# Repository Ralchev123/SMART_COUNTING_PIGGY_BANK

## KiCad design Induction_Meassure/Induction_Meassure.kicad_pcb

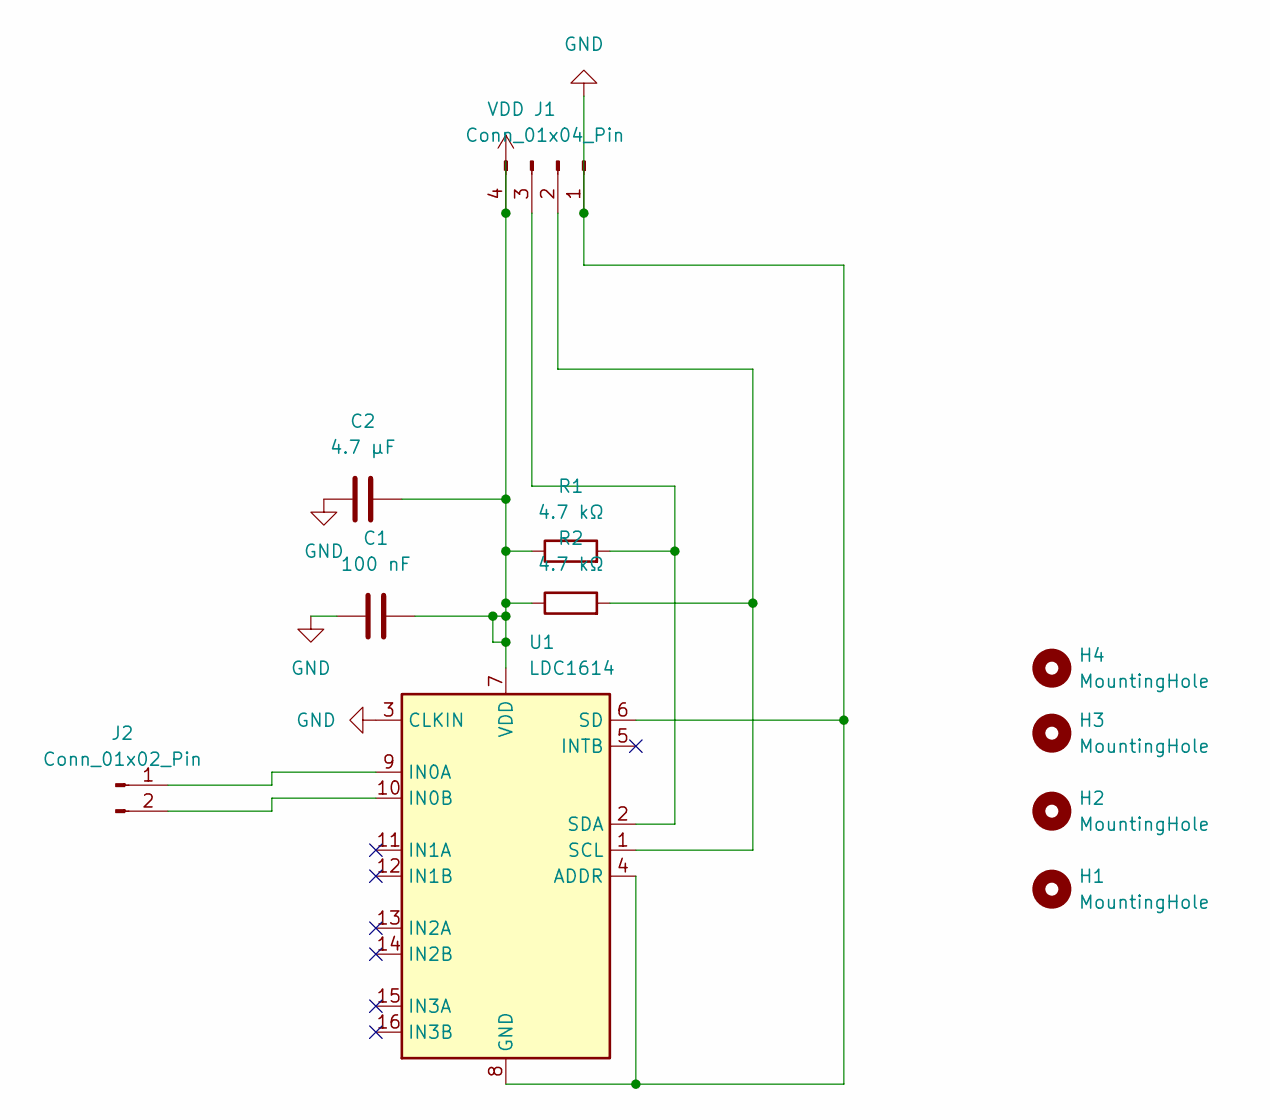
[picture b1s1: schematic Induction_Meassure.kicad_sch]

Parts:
C1: 100 nF; C_0603_1608Metric
C2: 4.7 µF; C_1206_3216Metric
H1, H2, H3, H4: MountingHole; MountingHole_3.2mm_M3
J1: Conn_01x04_Pin; PinHeader_1x04_P2.54mm_Vertical
J2: Conn_01x02_Pin; PinHeader_1x02_P2.54mm_Vertical
R1, R2: 4.7 kΩ; R_0805_2012Metric
U1: LDC1614; WQFN-16-1EP_4x4mm_P0.5mm_EP2.6x2.6mm_ThermalVias

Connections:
GND: C1.1, C2.2, J1.1, U1.3 (CLKIN), U1.4 (ADDR), U1.6 (SD), U1.8 (GND), U1.17 (GND)
unnamed: J1.2, R2.2, U1.1 (SCL)
unnamed: J1.3, R1.2, U1.2 (SDA)
unnamed: J2.1, U1.9 (IN0A)
unnamed: J2.2, U1.10 (IN0B)
VDD: C1.2, C2.1, J1.4, R1.1, R2.1, U1.7 (VDD)

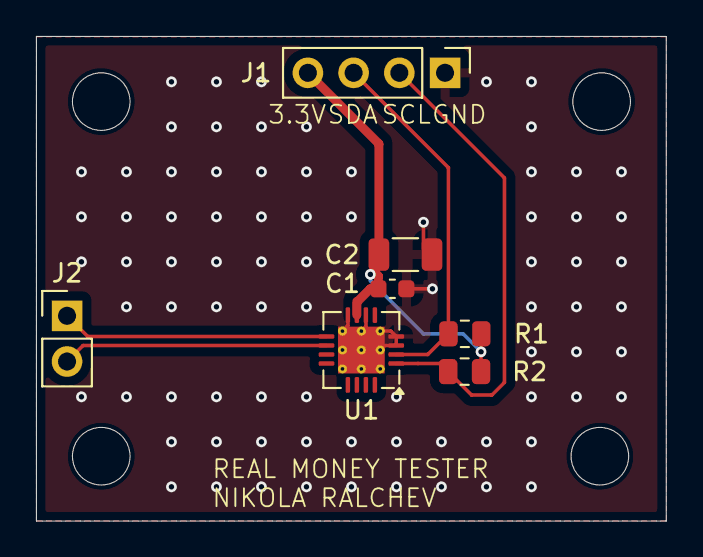
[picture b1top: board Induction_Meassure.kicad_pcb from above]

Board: 2 copper layers, 35.0 x 26.9 mm, 11 parts (0 on the bottom side), 6 nets.

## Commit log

2025-12-01 The file for the sorter frame
2025-12-01 Create test
2025-12-01 Main Sled, Coin Slot and the sorting frame
2025-12-10 Zip folder of the KiCad project
2025-12-18 Main 3d Files of the Collection Box
2026-01-20 Finalize ESP32 firmware
    inductive auth, optical counting, NVS persistence, gesture reset
2026-02-09 Create LICENSE
